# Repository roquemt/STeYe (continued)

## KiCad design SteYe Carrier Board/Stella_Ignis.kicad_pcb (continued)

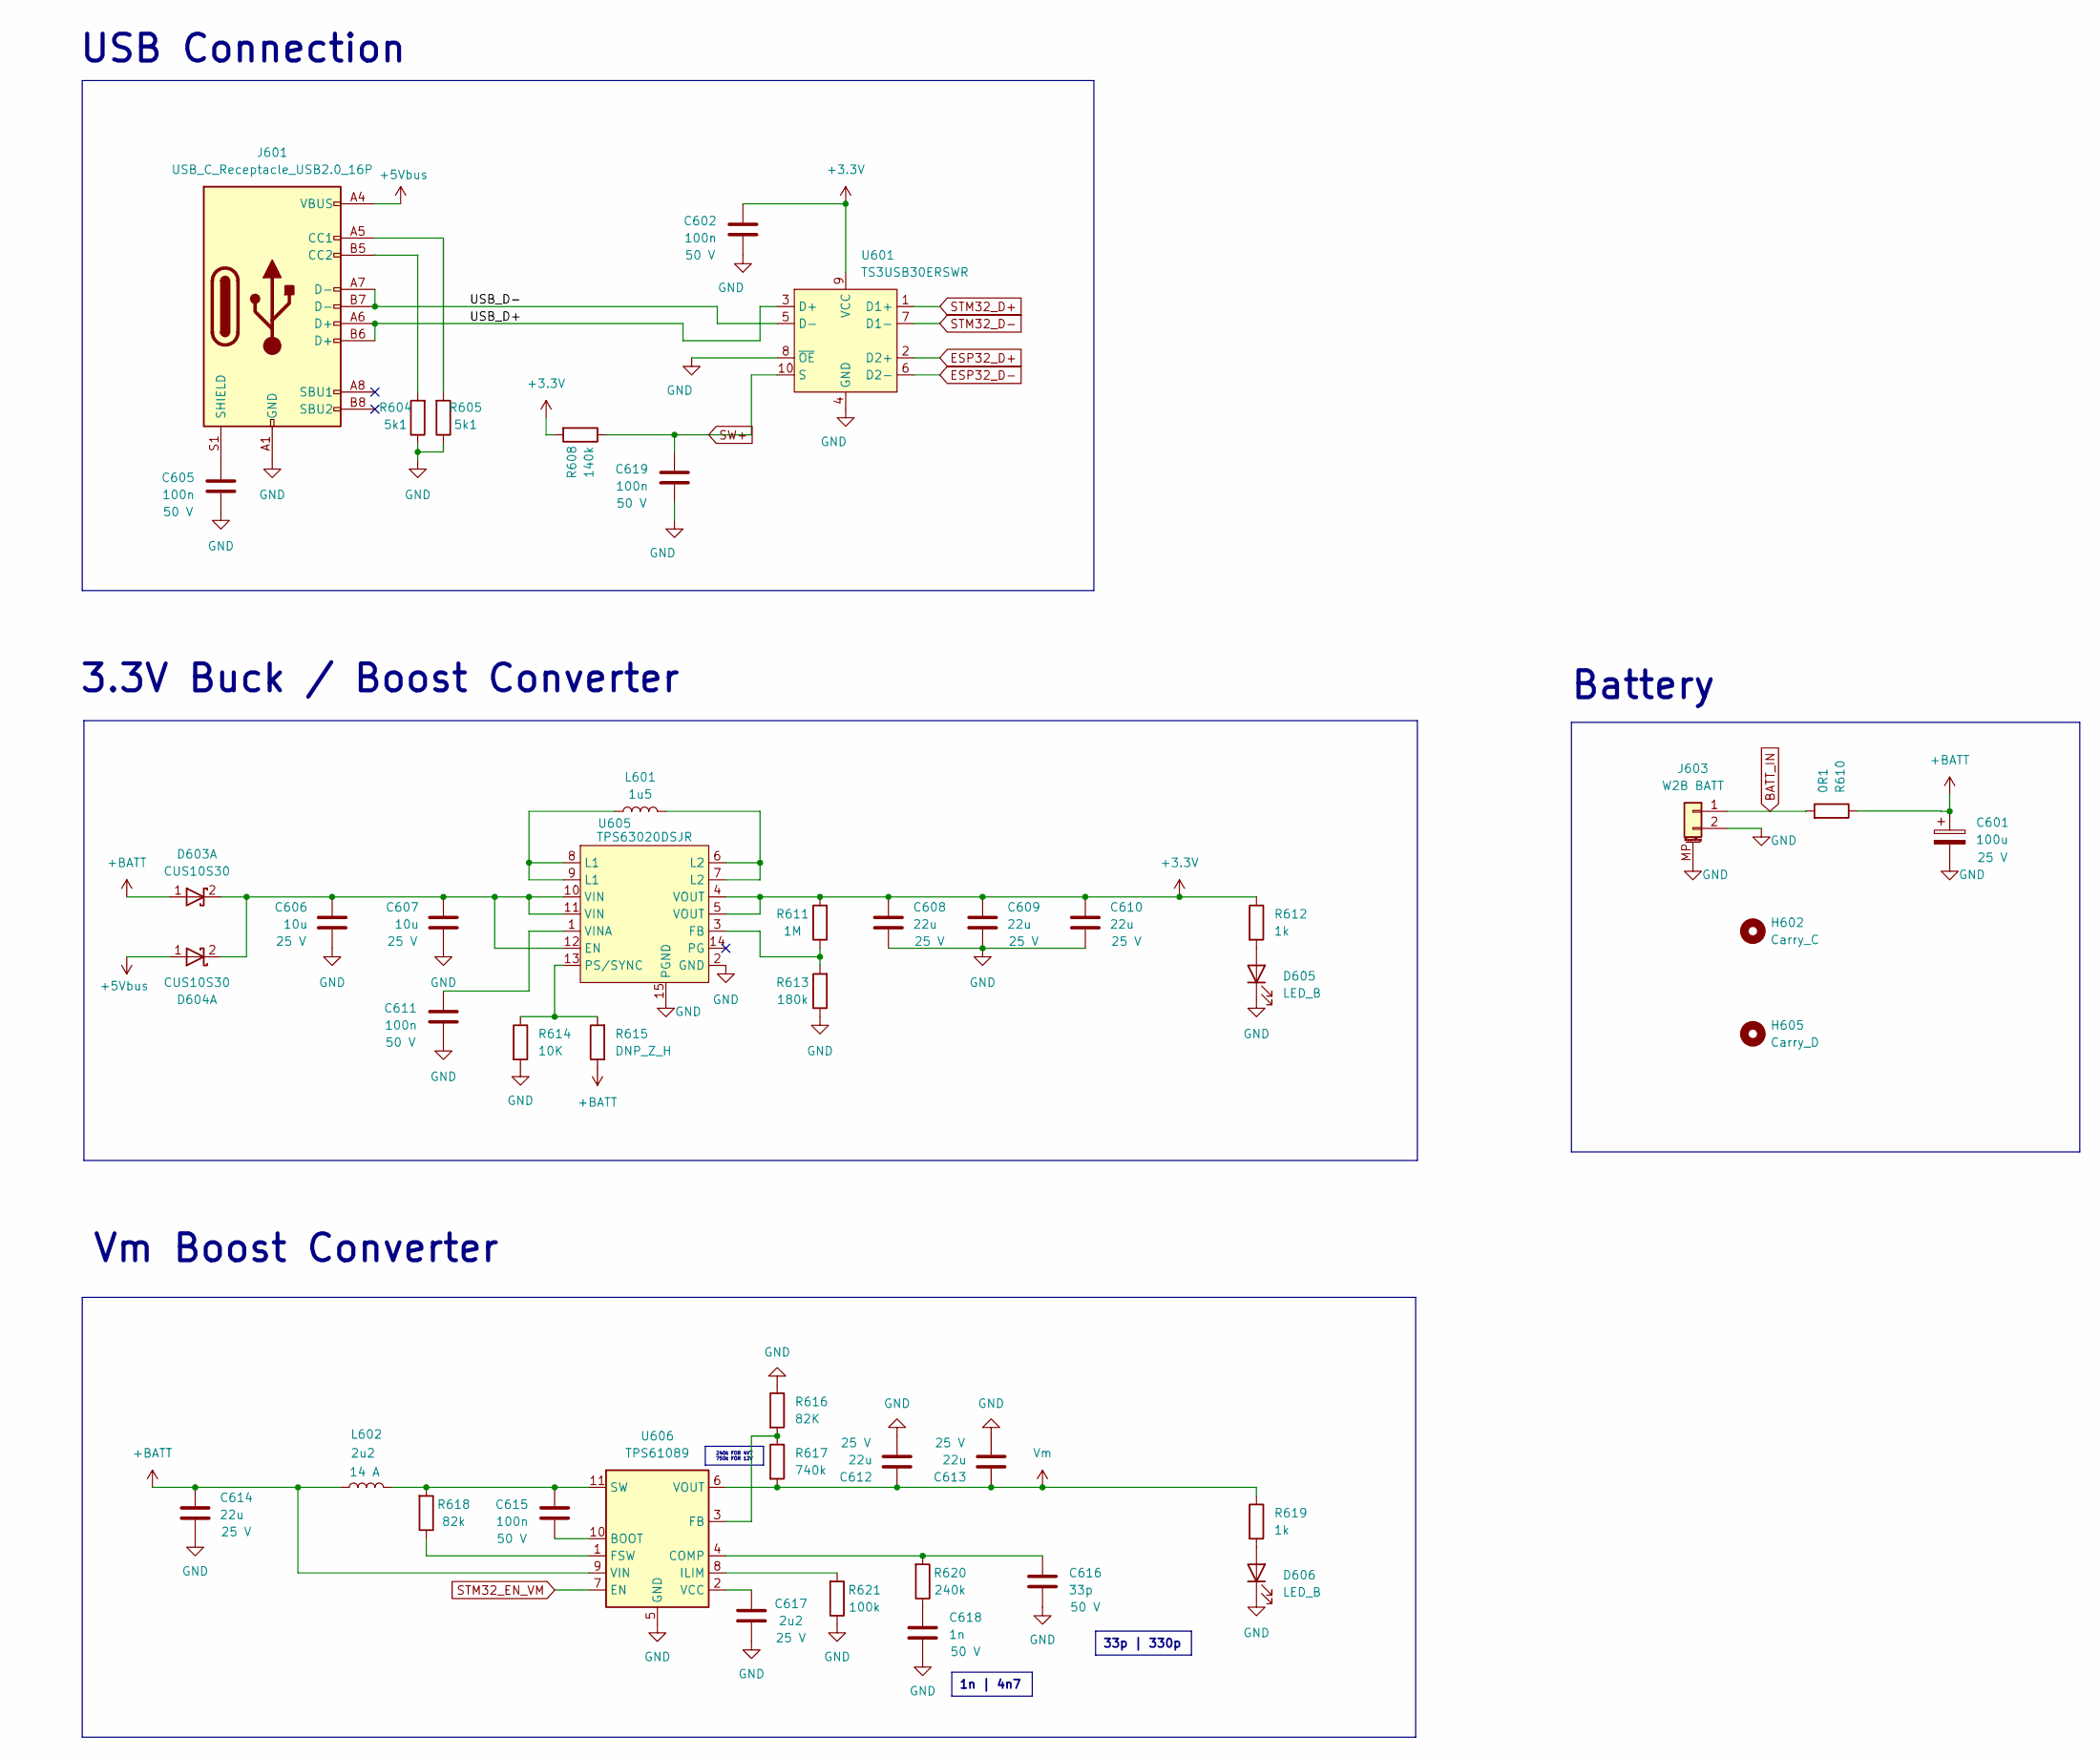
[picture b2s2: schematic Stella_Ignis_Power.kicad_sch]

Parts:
C601: 100u; CP_EIA-6032-15_Kemet-U_Pad2.25x2.35mm_HandSolder; Voltage 25 V
C602, C605, C611, C615, C619: 100n; C_0402_1005Metric; Voltage 50 V
C606, C607: 10u; C_0402_1005Metric; Voltage 25 V
C608, C609, C610, C612, C613, C614: 22u; C_0805_2012Metric; Voltage 25 V
C616: 33p; C_0402_1005Metric; Voltage 50 V
C617: 2u2; C_0402_1005Metric; Voltage 25 V
C618: 1n; C_0402_1005Metric; Voltage 50 V
D603, D604: CUS10S30; D_SOD-323
D605, D606: LED_B; D_0603_1608Metric
H602: Carry_C; MountingHole_2.2mm_M2
H605: Carry_D; MountingHole_2.2mm_M2
J601: USB_C_Receptacle_USB2.0_16P; USB_C_Receptacle_GCT_USB4105-xx-A_16P_TopMnt_Horizontal
J603: W2B BATT; Molex_PicoBlade_53261-0271_1x02-1MP_P1.25mm_Horizontal
L601: 1u5; Inductor SLO201610T1R5MTT
L602: 2u2; L_Sunlord_MWSA0605S
R604, R605: 5k1; R_0402_1005Metric
R608: 140k; R_0402_1005Metric
R610: 0R1; R_0805_2012Metric
R611: 1M; R_0402_1005Metric
R612, R619: 1k; R_0402_1005Metric
R613: 180k; R_0402_1005Metric
R614: 10K; R_0402_1005Metric
R615: DNP_Z_H; R_0402_1005Metric
R616: 82K; R_0402_1005Metric
R617: 740k; R_0402_1005Metric
R618: 82k; R_0402_1005Metric
R620: 240k; R_0402_1005Metric
R621: 100k; R_0402_1005Metric
U601: TS3USB30ERSWR; UQFN-10_1.4x1.8mm_P0.4mm
U605: TPS63020DSJR
U606: TPS61089; Texas_VQFN-RNR0011A-11

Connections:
+3.3V: C602.1, C608.1, C609.1, C610.1, R608.2, R611.2, R612.1, U601.9 (VCC), U605.4 (VOUT), U605.5 (VOUT); also elsewhere on the board
+5Vbus: D604.1 (A), J601.A4 (VBUS), J601.A9 (VBUS), J601.B4 (VBUS), J601.B9 (VBUS)
+BATT: C601.1, C614.1, D603.1 (A), L602.1, R610.1, R615.1, U606.9 (VIN); also elsewhere on the board
/Power Stage/USB_D+: J601.A6 (D+), J601.B6 (D+), U601.3 (D+)
/Power Stage/USB_D-: J601.A7 (D-), J601.B7 (D-), U601.5 (D-)
BATT_IN: J603.1, R610.2; also elsewhere on the board
ESP32_D+: U601.2 (D2+); also elsewhere on the board
ESP32_D-: U601.6 (D2-); also elsewhere on the board
GND: C601.2, C602.2, C605.2, C606.2, C607.2, C608.2, C609.2, C610.2, C611.2, C612.2, C613.2, C614.2, C616.2, C617.2, C618.2, C619.2, D605.1 (K), D606.1 (K), J601.A1 (GND), J601.A12 (GND), J601.B1 (GND), J601.B12 (GND), J603.2, J603.MP (MountPin), R604.1, R605.1, R613.1, R614.2, R616.1, R621.1, U601.4 (GND), U601.8 (~OE), U605.2 (GND), U605.15 (PGND), U606.5 (GND); also elsewhere on the board
unnamed: C618.1, R620.1
unnamed: C606.1, C607.1, D603.2 (K), D604.2 (K), U605.10 (VIN), U605.11 (VIN), U605.12 (EN)
unnamed: D605.2 (A), R612.2
unnamed: D606.2 (A), R619.2
unnamed: J601.A5 (CC1), R605.2
unnamed: J601.B5 (CC2), R604.2
unnamed: C605.1, J601.S1 (SHIELD)
unnamed: L601.1, U605.8 (L1), U605.9 (L1)
unnamed: L601.2, U605.6 (L2), U605.7 (L2)
unnamed: R611.1, R613.2, U605.3 (FB)
unnamed: R614.1, R615.2, U605.13 (PS/SYNC)
unnamed: C611.1, U605.1 (VINA)
unnamed: C615.2, U606.10 (BOOT)
unnamed: C616.1, R620.2, U606.4 (COMP)
unnamed: R616.2, R617.1, U606.3 (FB)
unnamed: R618.1, U606.1 (FSW)
unnamed: R621.2, U606.8 (ILIM)
unnamed: C615.1, L602.2, R618.2, U606.11 (SW)
unnamed: C617.1, U606.2 (VCC)
STM32_D+: U601.1 (D1+); also elsewhere on the board
STM32_D-: U601.7 (D1-); also elsewhere on the board
STM32_EN_VM: U606.7 (EN); also elsewhere on the board
SW+: C619.1, R608.1, U601.10 (S); also elsewhere on the board
Vm: C612.1, C613.1, R617.2, R619.1, U606.6 (VOUT); also elsewhere on the board

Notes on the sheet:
33p | 330p
240k FOR 4V7 750k FOR 12V
1n | 4n7
USB Connection
Vm Boost Converter
Battery
3.3V Buck / Boost Converter

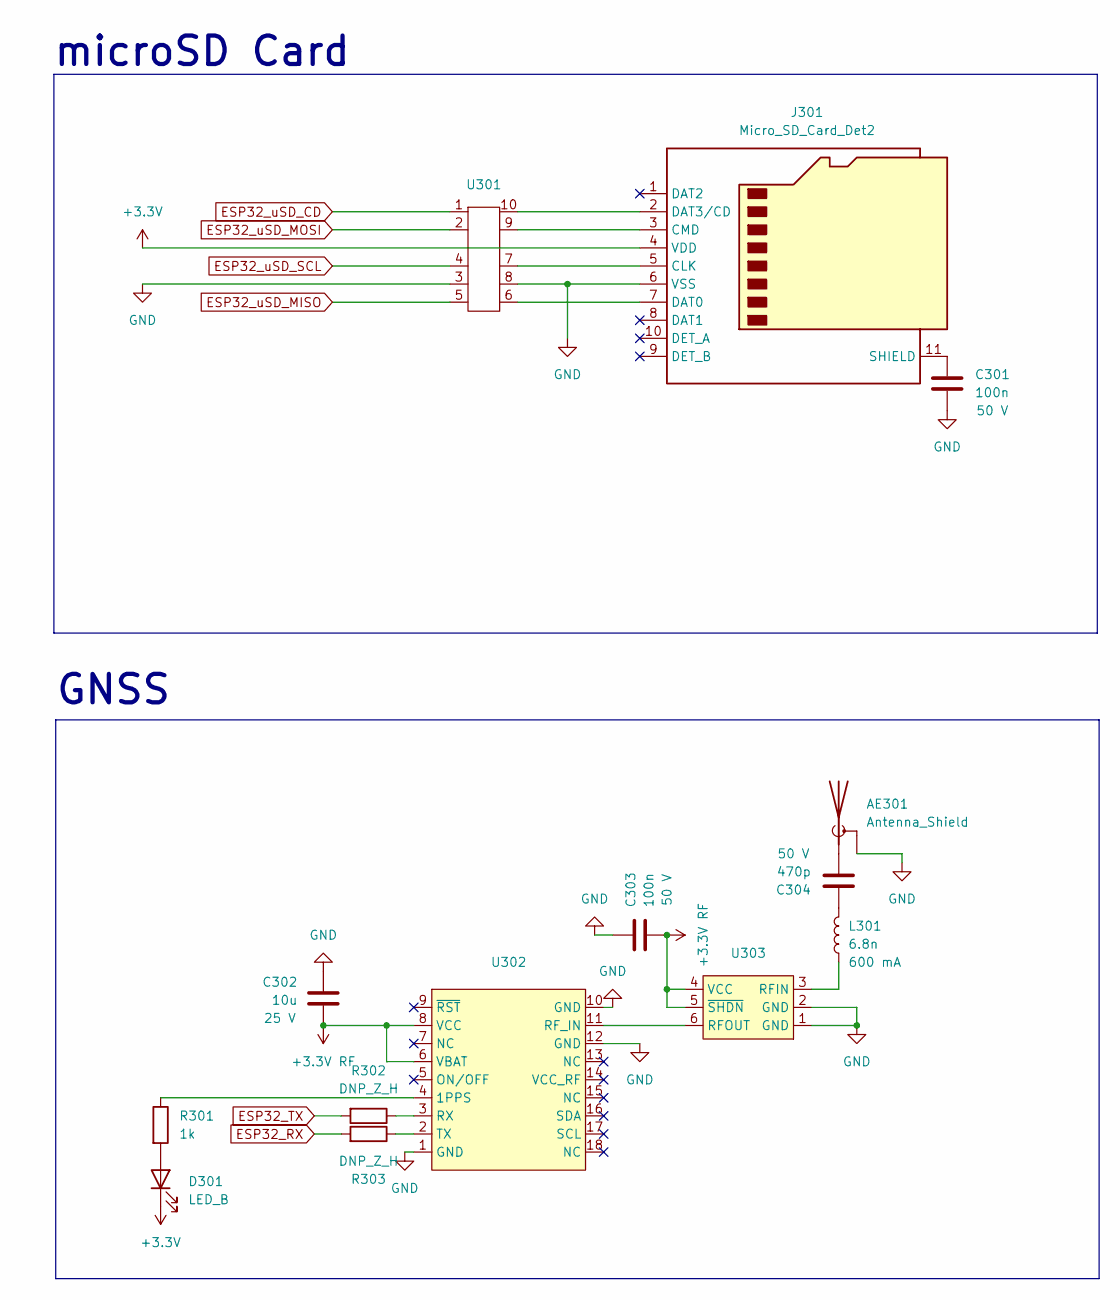
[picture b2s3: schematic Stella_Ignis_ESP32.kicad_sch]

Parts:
AE301: Antenna_Shield; U.FL_Hirose_U.FL-R-SMT-1_Vertical
C301, C303: 100n; C_0402_1005Metric; Voltage 50 V
C302: 10u; C_0402_1005Metric; Voltage 25 V
C304: 470p; C_0402_1005Metric; Voltage 50 V
D301: LED_B; D_0603_1608Metric
J301: Micro_SD_Card_Det2; microSD_HC_Hirose_DM3D-SF
L301: 6.8n; L_0402_1005Metric
R301: 1k; R_0402_1005Metric
R302, R303: DNP_Z_H; R_0402_1005Metric
U301: Diodes_UDFN-10_1.0x2.5mm_P0.5mm
U302: ATGM336H
U303: DFN-6-1EP_2x2mm_P0.5mm_EP0.61x1.42mm

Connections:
+3.3V: D301.1 (K), J301.4 (VDD); also elsewhere on the board
+3.3V RF: C302.2, C303.2, U302.6 (VBAT), U302.8 (VCC), U303.4 (VCC), U303.5 (~SHDN); also elsewhere on the board
ESP32_RX: R303.2; also elsewhere on the board
ESP32_TX: R302.2; also elsewhere on the board
ESP32_uSD_CD: U301.1; also elsewhere on the board
ESP32_uSD_MISO: U301.5; also elsewhere on the board
ESP32_uSD_MOSI: U301.2; also elsewhere on the board
ESP32_uSD_SCL: U301.4; also elsewhere on the board
GND: AE301.2 (Shield), C301.2, C302.1, C303.1, J301.6 (VSS), U301.3, U301.8, U302.1 (GND), U302.10 (GND), U302.12 (GND), U303.1 (GND), U303.2 (GND); also elsewhere on the board
unnamed: AE301.1 (A), C304.2
unnamed: C304.1, L301.2
unnamed: D301.2 (A), R301.2
unnamed: J301.5 (CLK), U301.7
unnamed: J301.3 (CMD), U301.9
unnamed: J301.7 (DAT0), U301.6
unnamed: J301.2 (DAT3/CD), U301.10
unnamed: C301.1, J301.11 (SHIELD)
unnamed: R301.1, U302.4 (1PPS)
unnamed: U302.11 (RF_IN), U303.6 (RFOUT)
unnamed: R302.1, U302.3 (RX)
unnamed: R303.1, U302.2 (TX)
unnamed: L301.1, U303.3 (RFIN)

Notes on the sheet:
microSD Card
GNSS

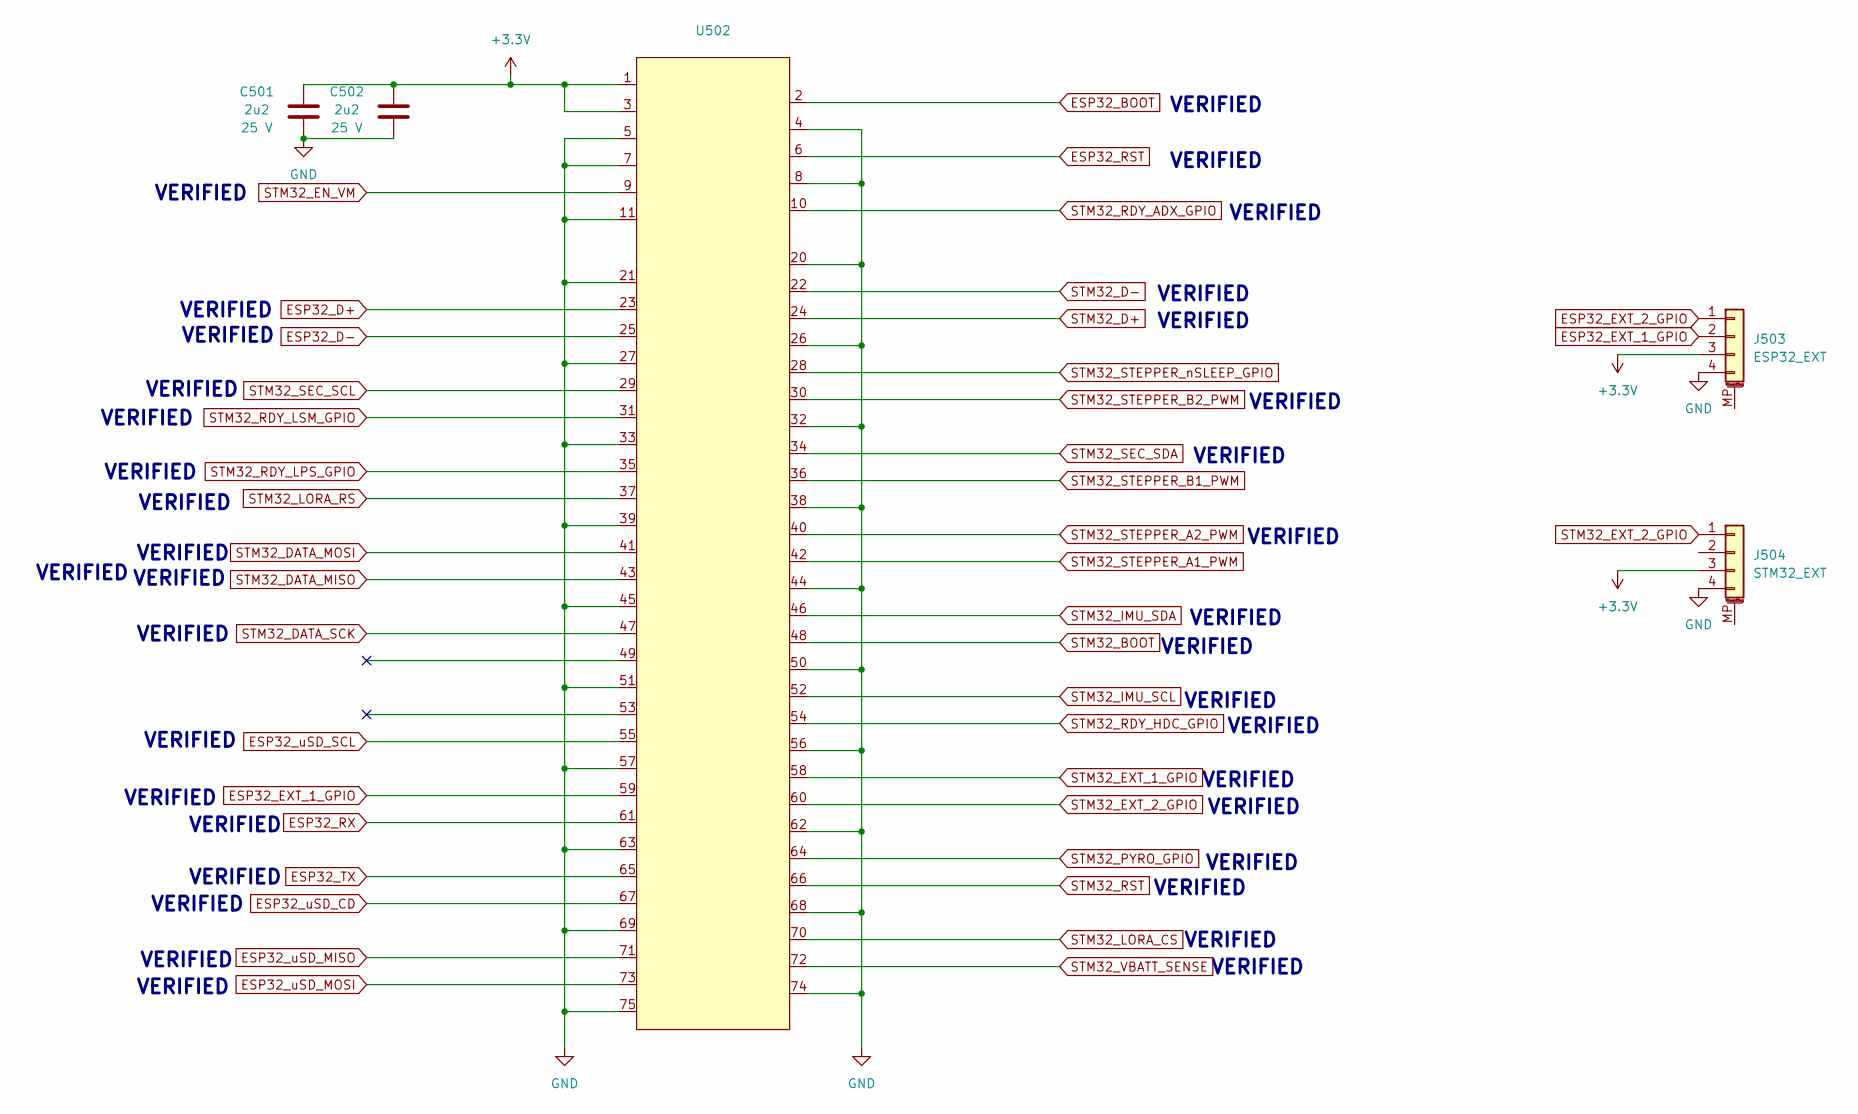
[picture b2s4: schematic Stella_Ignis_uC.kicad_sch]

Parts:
C501, C502: 2u2; C_0402_1005Metric; Voltage 25 V
J503: ESP32_EXT; Molex_PicoBlade_53261-0471_1x04-1MP_P1.25mm_Horizontal
J504: STM32_EXT; Molex_PicoBlade_53261-0471_1x04-1MP_P1.25mm_Horizontal
U502: TE M.2 Key B

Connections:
+3.3V: C501.2, C502.2, J503.3, J504.3, U502.1, U502.3; also elsewhere on the board
ESP32_BOOT: U502.2; also elsewhere on the board
ESP32_D+: U502.23; also elsewhere on the board
ESP32_D-: U502.25; also elsewhere on the board
ESP32_EXT_1_GPIO: J503.2, U502.59
ESP32_RST: U502.6; also elsewhere on the board
ESP32_RX: U502.61; also elsewhere on the board
ESP32_TX: U502.65; also elsewhere on the board
ESP32_uSD_CD: U502.67; also elsewhere on the board
ESP32_uSD_MISO: U502.71; also elsewhere on the board
ESP32_uSD_MOSI: U502.73; also elsewhere on the board
ESP32_uSD_SCL: U502.55; also elsewhere on the board
GND: C501.1, C502.1, J503.4, J504.4, U502.4, U502.5, U502.7, U502.8, U502.11, U502.20, U502.21, U502.26, U502.27, U502.32, U502.33, U502.38, U502.39, U502.44, U502.45, U502.50, U502.51, U502.56, U502.57, U502.62, U502.63, U502.68, U502.69, U502.74, U502.75; also elsewhere on the board
STM32_BOOT: U502.48; also elsewhere on the board
STM32_D+: U502.24; also elsewhere on the board
STM32_D-: U502.22; also elsewhere on the board
STM32_DATA_MISO: U502.43; also elsewhere on the board
STM32_DATA_MOSI: U502.41; also elsewhere on the board
STM32_DATA_SCK: U502.47; also elsewhere on the board
STM32_EN_VM: U502.9; also elsewhere on the board
STM32_EXT_1_GPIO: U502.58
STM32_EXT_2_GPIO: J504.1, U502.60
STM32_IMU_SCL: U502.52; also elsewhere on the board
STM32_IMU_SDA: U502.46; also elsewhere on the board
STM32_LORA_CS: U502.70; also elsewhere on the board
STM32_LORA_RS: U502.37; also elsewhere on the board
STM32_PYRO_GPIO: U502.64; also elsewhere on the board
STM32_RDY_ADX_GPIO: U502.10; also elsewhere on the board
STM32_RDY_HDC_GPIO: U502.54; also elsewhere on the board
STM32_RDY_LPS_GPIO: U502.35; also elsewhere on the board
STM32_RDY_LSM_GPIO: U502.31; also elsewhere on the board
STM32_RST: U502.66; also elsewhere on the board
STM32_SEC_SCL: U502.29; also elsewhere on the board
STM32_SEC_SDA: U502.34; also elsewhere on the board
STM32_STEPPER_A1_PWM: U502.42; also elsewhere on the board
STM32_STEPPER_A2_PWM: U502.40; also elsewhere on the board
STM32_STEPPER_B1_PWM: U502.36; also elsewhere on the board
STM32_STEPPER_B2_PWM: U502.30; also elsewhere on the board
STM32_STEPPER_nSLEEP_GPIO: U502.28
STM32_VBATT_SENSE: U502.72; also elsewhere on the board

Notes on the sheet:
VERIFIED

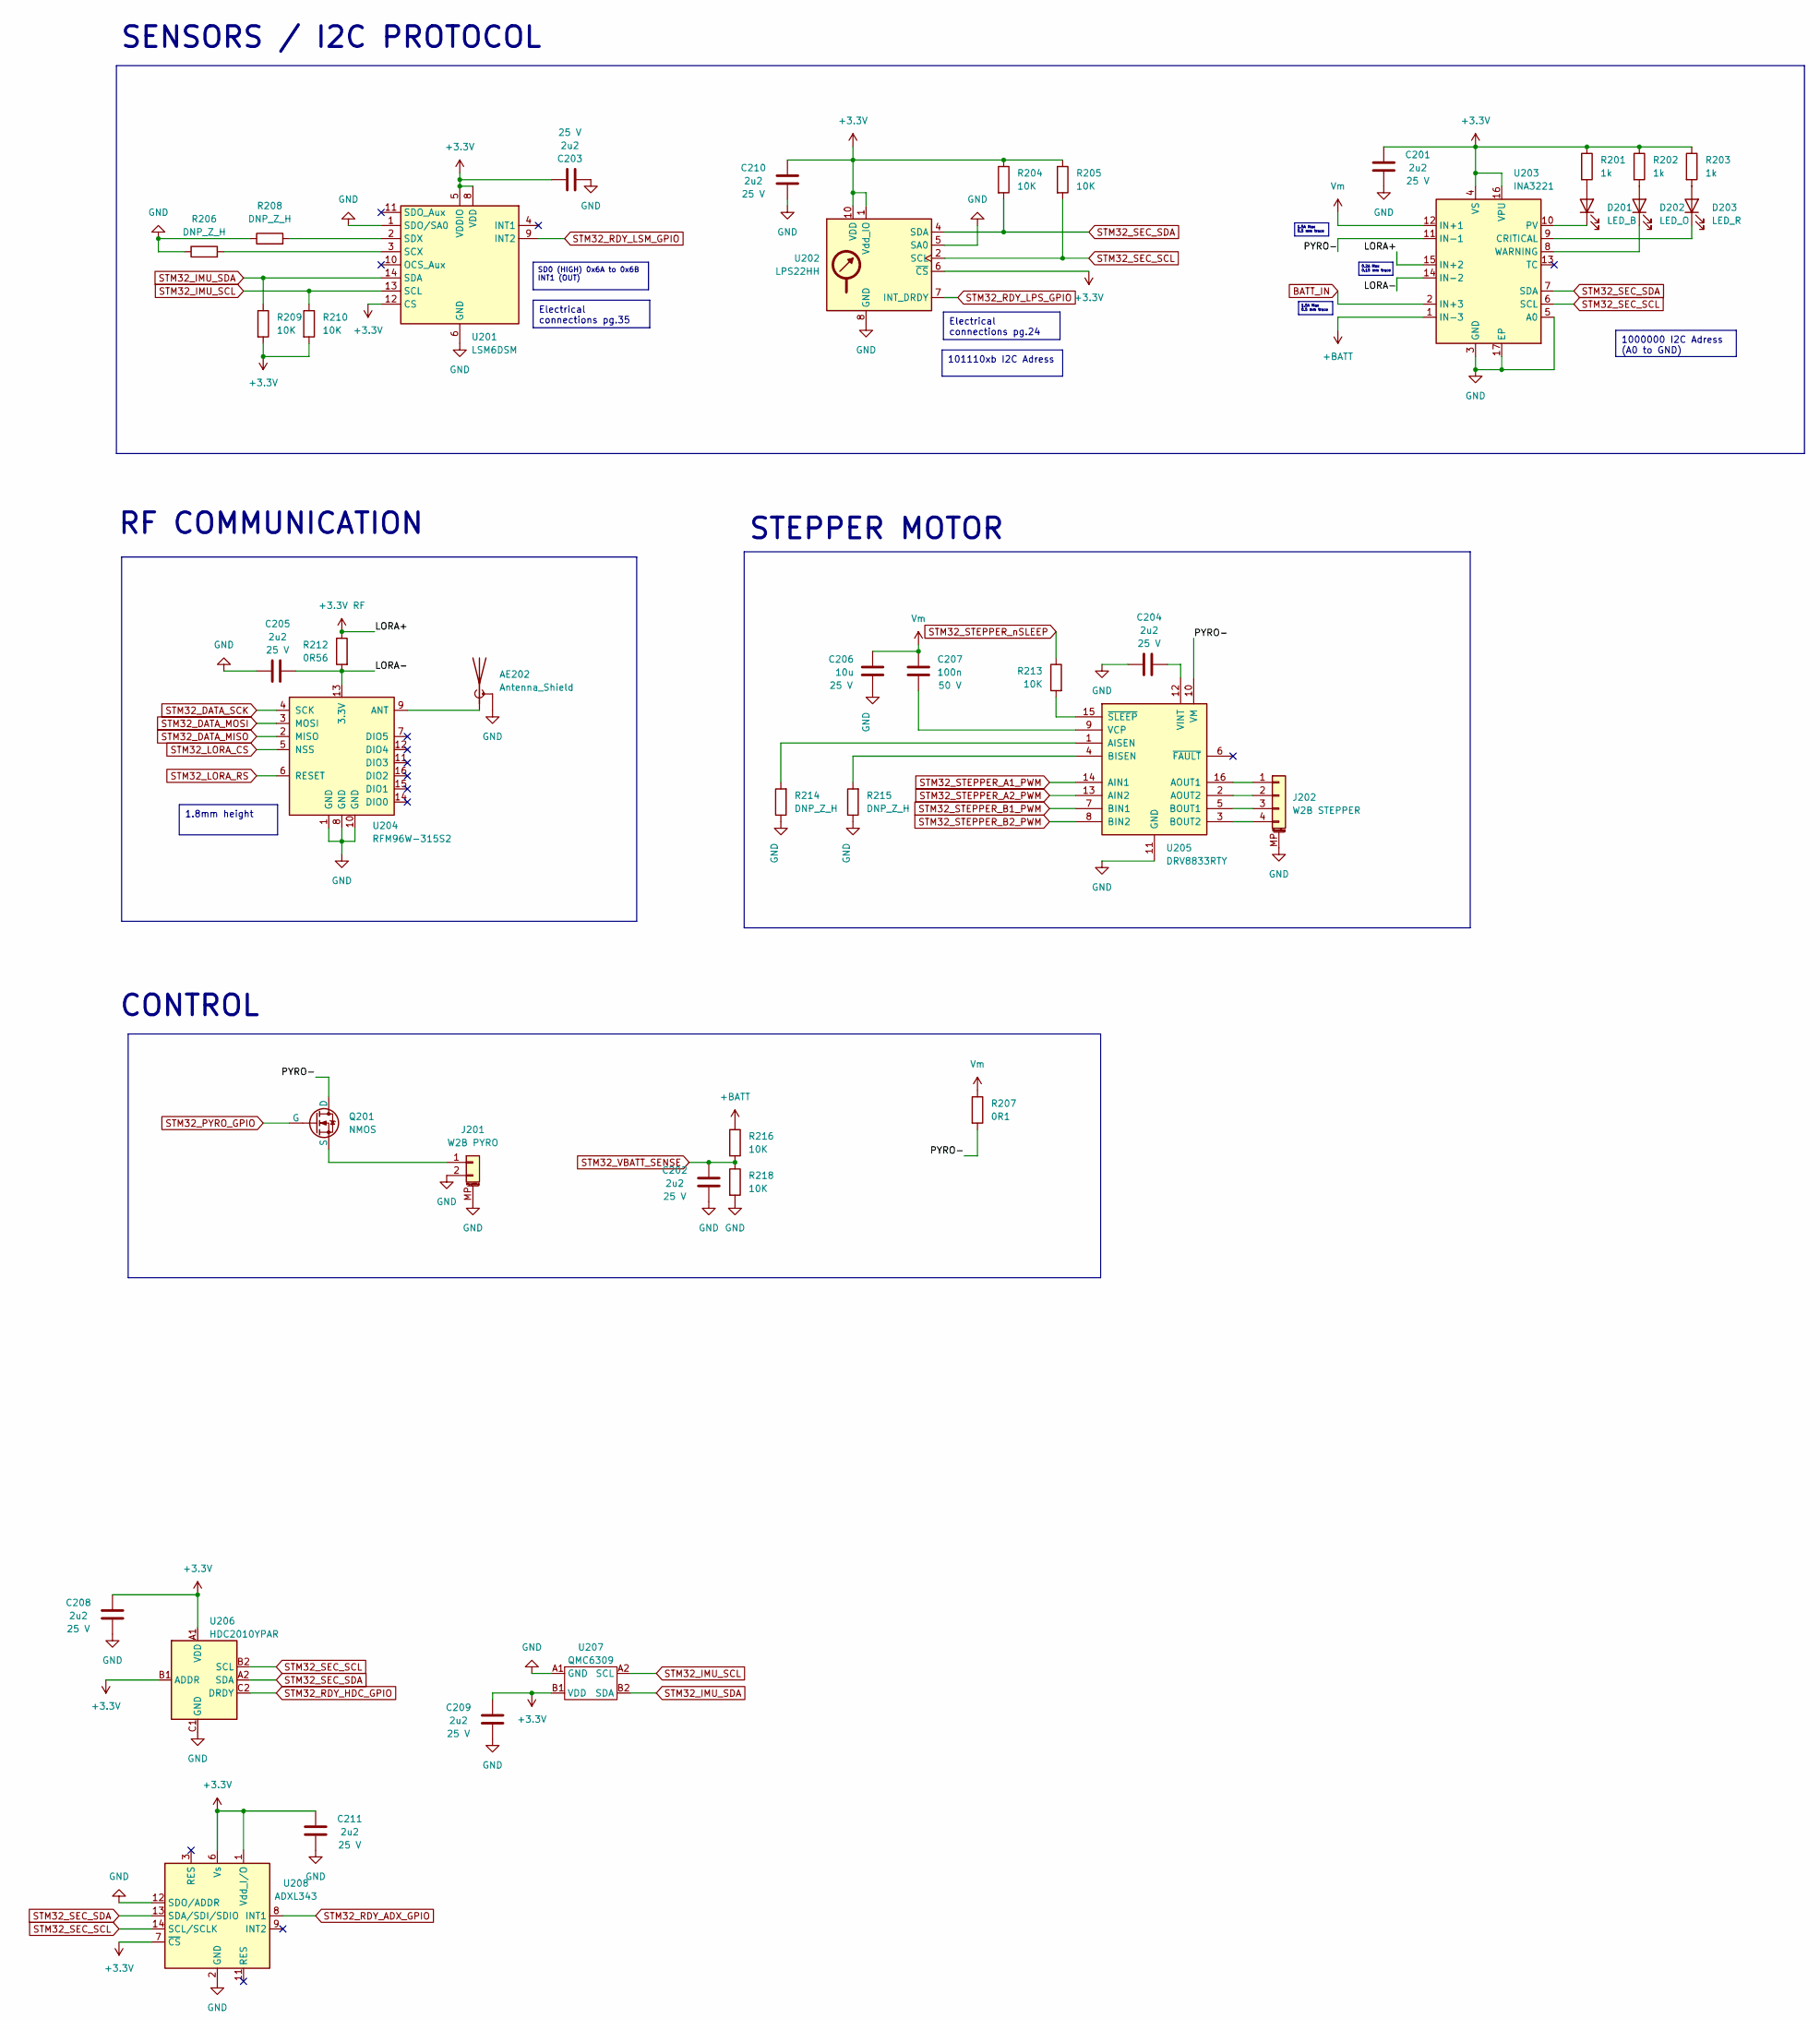
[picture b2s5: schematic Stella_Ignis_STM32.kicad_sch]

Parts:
AE202: Antenna_Shield; U.FL_Hirose_U.FL-R-SMT-1_Vertical
C201, C202, C203, C204, C205, C208, C209, C210, C211: 2u2; C_0402_1005Metric; Voltage 25 V
C206: 10u; C_0603_1608Metric; Voltage 25 V
C207: 100n; C_0402_1005Metric; Voltage 50 V
D201: LED_B; D_0603_1608Metric
D202: LED_O; D_0603_1608Metric
D203: LED_R; D_0603_1608Metric
J201: W2B PYRO; Molex_PicoBlade_53261-0271_1x02-1MP_P1.25mm_Horizontal
J202: W2B STEPPER; Molex_PicoBlade_53261-0471_1x04-1MP_P1.25mm_Horizontal
Q201: NMOS; SOT-23
R201, R202, R203: 1k; R_0402_1005Metric
R204, R205, R209, R210, R213, R216, R218: 10K; R_0402_1005Metric
R206, R208, R214, R215: DNP_Z_H; R_0402_1005Metric
R207: 0R1; R_0805_2012Metric
R212: 0R56; R_0805_2012Metric
U201: LSM6DSM; LGA-14_3x2.5mm_P0.5mm_LayoutBorder3x4y
U202: LPS22HH; ST_HLGA-10_2x2mm_P0.5mm_LayoutBorder3x2y
U203: INA3221; Texas_RGV0016A_VQFN-16-1EP_4x4mm_P0.65mm_EP2.1x2.1mm
U204: RFM96W-315S2; MODULE_RFM96W-433S2
U205: DRV8833RTY; Texas_RTY_WQFN-16-1EP_4x4mm_P0.65mm_EP2.1x2.1mm
U206: HDC2010YPAR; Texas_DSBGA-6_0.9x1.4mm_Layout2x3_P0.5mm
U207: QMC6309; WLCSP-4-X1-WLB0909-4_0.89x0.89mm_P0.5mm
U208: ADXL343; LGA-14_3x5mm_P0.8mm_LayoutBorder1x6y

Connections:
+3.3V: C201.1, C203.2, C208.1, C209.1, C210.1, C211.1, R201.1, R202.1, R203.1, R204.1, R205.1, R209.2, R210.2, U201.5 (VDDIO), U201.8 (VDD), U201.12 (CS), U202.1 (Vdd_IO), U202.6 (~CS), U202.10 (VDD), U203.4 (VS), U203.16 (VPU), U206.A1 (VDD), U206.B1 (ADDR), U207.B1 (VDD), U208.1 (Vdd_I/O), U208.6 (Vs), U208.7 (~CS); also elsewhere on the board
+3.3V RF: R212.1, U203.15 (IN+2); also elsewhere on the board
+BATT: R216.1, U203.1 (IN-3); also elsewhere on the board
/STM32/LORA-: C205.2, R212.2, U203.14 (IN-2), U204.13 (3.3V)
/STM32/PYRO-: Q201.1 (D), R207.2, U203.11 (IN-1), U205.10 (VM)
BATT_IN: U203.2 (IN+3); also elsewhere on the board
GND: AE202.2 (Shield), C201.2, C202.2, C203.1, C204.1, C205.1, C206.2, C208.2, C209.2, C210.2, C211.2, J201.2, J201.MP (MountPin), J202.MP (MountPin), R206.1, R208.1, R214.1, R215.1, R218.2, U201.1 (SDO/SA0), U201.6 (GND), U201.7 (GND), U202.3 (GND), U202.5 (SA0), U202.8 (GND), U202.9 (GND), U203.3 (GND), U203.5 (A0), U203.17 (EP), U204.1 (GND), U204.8 (GND), U204.10 (GND), U205.11 (GND), U205.17 (GND), U206.C1 (GND), U207.A1 (GND), U208.2 (GND), U208.4 (GND), U208.5 (GND), U208.12 (SDO/ADDR); also elsewhere on the board
unnamed: AE202.1 (A), U204.9 (ANT)
unnamed: D201.2 (A), R201.2
unnamed: D201.1 (K), U203.10 (PV)
unnamed: D202.2 (A), R202.2
unnamed: D202.1 (K), U203.8 (WARNING)
unnamed: D203.2 (A), R203.2
unnamed: D203.1 (K), U203.9 (CRITICAL)
unnamed: J201.1, Q201.3 (S)
unnamed: J202.1, U205.16 (AOUT1)
unnamed: J202.2, U205.2 (AOUT2)
unnamed: J202.3, U205.5 (BOUT1)
unnamed: J202.4, U205.3 (BOUT2)
unnamed: R206.2, U201.3 (SCX)
unnamed: R208.2, U201.2 (SDX)
unnamed: R214.2, U205.1 (AISEN)
unnamed: R215.2, U205.4 (BISEN)
unnamed: C207.2, U205.9 (VCP)
unnamed: C204.2, U205.12 (VINT)
unnamed: R213.2, U205.15 (~SLEEP)
STM32_DATA_MISO: U204.2 (MISO); also elsewhere on the board
STM32_DATA_MOSI: U204.3 (MOSI); also elsewhere on the board
STM32_DATA_SCK: U204.4 (SCK); also elsewhere on the board
STM32_IMU_SCL: R210.1, U201.13 (SCL), U207.A2 (SCL); also elsewhere on the board
STM32_IMU_SDA: R209.1, U201.14 (SDA), U207.B2 (SDA); also elsewhere on the board
STM32_LORA_CS: U204.5 (NSS); also elsewhere on the board
STM32_LORA_RS: U204.6 (RESET); also elsewhere on the board
STM32_PYRO_GPIO: Q201.2 (G); also elsewhere on the board
STM32_RDY_ADX_GPIO: U208.8 (INT1); also elsewhere on the board
STM32_RDY_HDC_GPIO: U206.C2 (DRDY); also elsewhere on the board
STM32_RDY_LPS_GPIO: U202.7 (INT_DRDY); also elsewhere on the board
STM32_RDY_LSM_GPIO: U201.9 (INT2); also elsewhere on the board
STM32_SEC_SCL: R205.2, U202.2 (SCL), U203.6 (SCL), U206.B2 (SCL), U208.14 (SCL/SCLK); also elsewhere on the board
STM32_SEC_SDA: R204.2, U202.4 (SDA), U203.7 (SDA), U206.A2 (SDA), U208.13 (SDA/SDI/SDIO); also elsewhere on the board
STM32_STEPPER_A1_PWM: U205.14 (AIN1); also elsewhere on the board
STM32_STEPPER_A2_PWM: U205.13 (AIN2); also elsewhere on the board
STM32_STEPPER_B1_PWM: U205.7 (BIN1); also elsewhere on the board
STM32_STEPPER_B2_PWM: U205.8 (BIN2); also elsewhere on the board
STM32_STEPPER_nSLEEP: R213.1
STM32_VBATT_SENSE: C202.1, R216.2, R218.1; also elsewhere on the board
Vm: C206.1, C207.1, R207.1, U203.12 (IN+1); also elsewhere on the board

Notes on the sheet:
SD0 (HIGH) 0x6A to 0x6B INT1 (OUT)
Electrical connections pg.35
1.5A Max 0.5 mm trace
101110xb I2C Adress
1.8mm height
1000000 I2C Adress (A0 to GND)
Electrical connections pg.24
0.2A Max 0.15 mm trace
STEPPER MOTOR
CONTROL
SENSORS / I2C PROTOCOL
RF COMMUNICATION

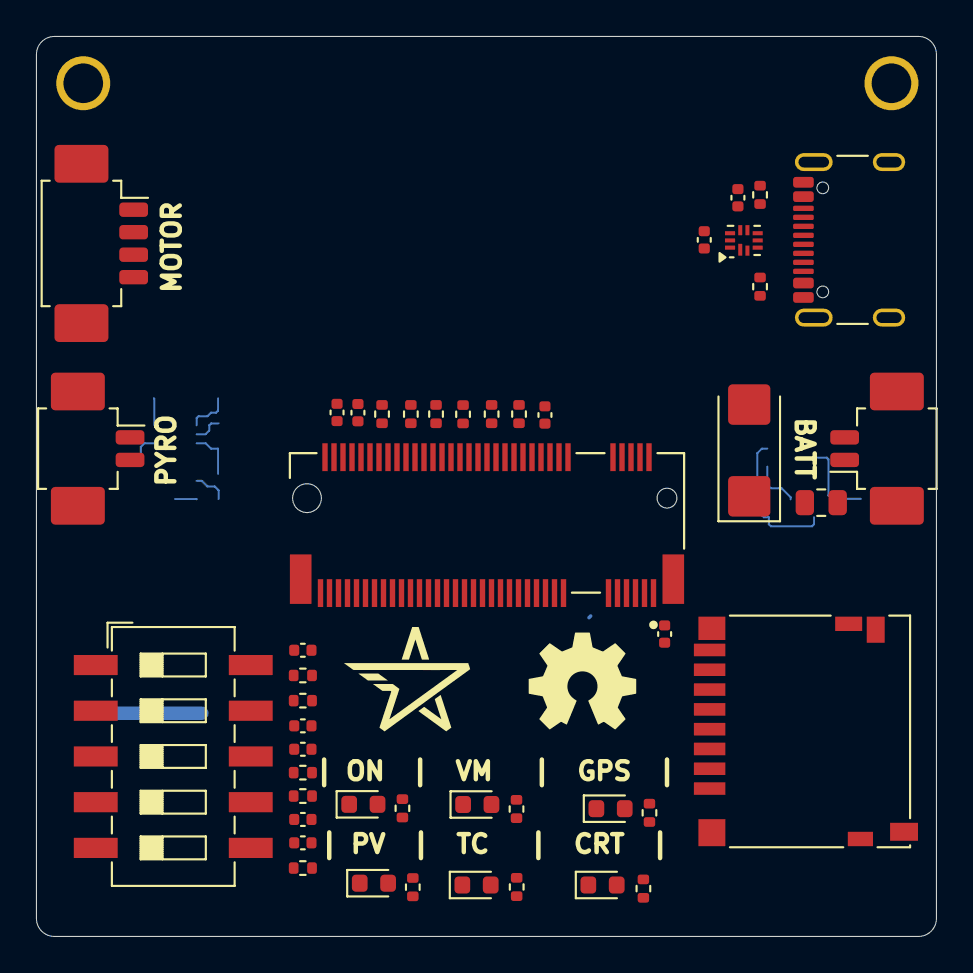
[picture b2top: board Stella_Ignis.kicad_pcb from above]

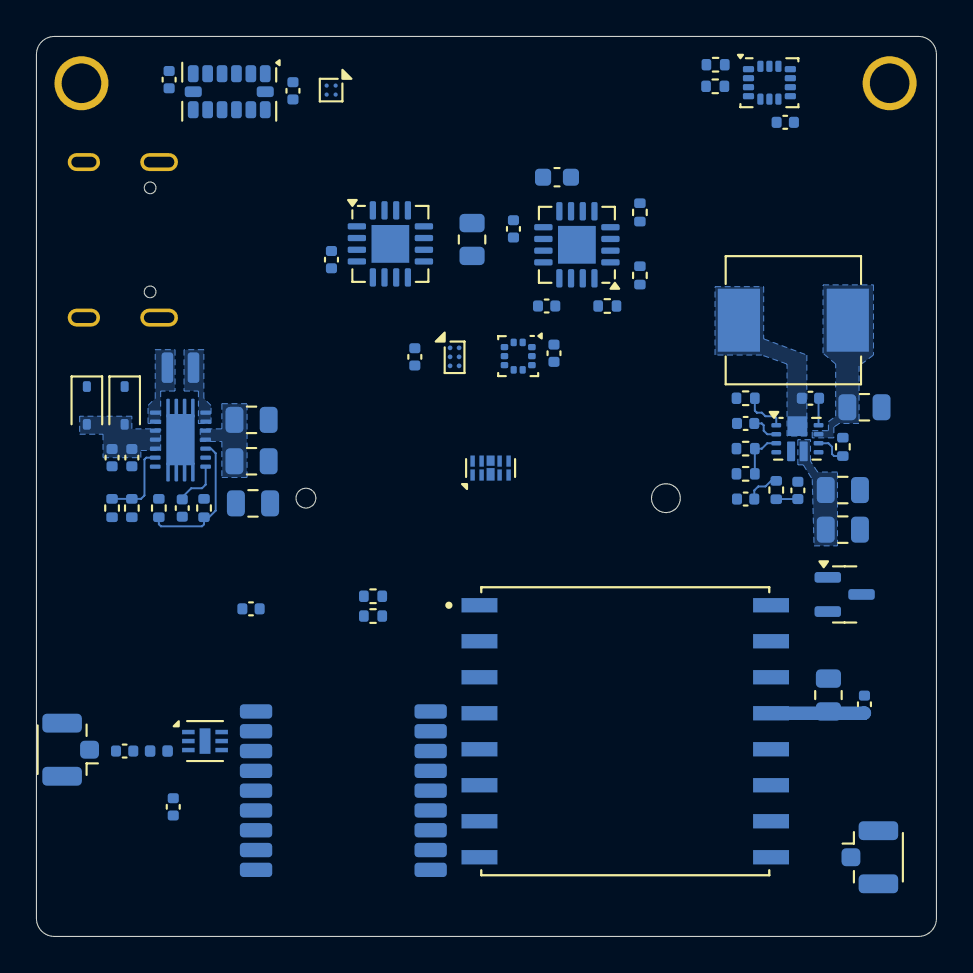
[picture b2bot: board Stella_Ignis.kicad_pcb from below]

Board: 8 copper layers, 50.0 x 50.0 mm, 113 parts (65 on the bottom side), 97 nets.
